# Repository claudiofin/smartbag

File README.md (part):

# SmartBag

**A removable smart insert for a handbag that recognises what is inside it —
without putting a tag on anything.**

Everything in this repo is generated by script: the PCB, the CAD, the renders,
the films. One command runs the whole chain, from KiCad to a finished MP4.

> *The GIF above is a short preview — click it for the full film.*
>
> **[▶ smartbag.mp4](media/smartbag.mp4)** (23 s) — how it is built ·
> **[▶ smartbag_sequence.mp4](media/smartbag_sequence.mp4)** (22 s) — how it works

---

## Read this first

This is a **design study**. Some of it is now checked by machine; none of it has
been built.

| | |
|---|---|
| schematic | **exists**, generated from `hardware/netlist.py`. **ERC: 0 violations.** |
| board | **113 footprints, six copper layers, routed, assembled on both sides.** DRC: **0 unconnected, 0 clearance violations, 0 shorts**; ERC clean. ⛔ It took a stackup change to get there, and the number that justified it is in [Six layers](#six-layers-and-the-number-that-decided-it). |
| part numbers | ⭐ **every IC is a real part, and its pinout comes from its own datasheet.** `tools/bom_report.py` measures each footprint against the datasheet's package on every run: **23 of 23 agree** — see [The bill of materials](#the-bill-of-materials). |
| firmware | the wake-up chain, the ledger, the taxel driver, the charge policy, the sensor bring-up, **the sensing loop that finally calls `sb_feed()`** and an Arducam Mega driver written from its own register table — **1035 assertions**, `-Werror`. ⭐ **And it builds for the nRF54L15**: [`firmware/target/`](firmware/target/) is a Zephyr app — ten HAL functions, the GATT service, the PMIC through Nordic's driver, a pin map **generated from the netlist** — at **177 KB of flash and 72 KB of RAM**, run by `tools/verify.sh`. ⚠️ Built, never run: nothing has met silicon. |
| recognition on the real part | the SoC has **no NPU**, so it was costed: 6.99 M MACs a frame on a 128 MHz M33 is **110–191 ms** against a settle window of 2000 ms — see [Recognition fits](#recognition-fits-the-processor). |
| recognition | an **enrolment pipeline that runs and is measured** — see [Recognition](#recognition). ⚠️ It now has to run on a Cortex-M33, not an NPU. |
| app | **written and running** — [`app/`](app/), tested against the firmware's own bytes. No native build; it is a web app. |
| RF | full-wave simulation rejected the antenna, closed-form analysis then rejected the whole feed — and the real part **dissolved the problem**: 60 GHz silicon has the antenna inside the package. There is now **no 60 GHz copper on this board.** See [RF](#rf). |
| thermal | **analysed** ([`thermal/budget.py`](thermal/budget.py)). It asked for charge current to be a function of cell temperature; the cell now has an NTC **in the pack**, a PMIC that reads it, and a policy under 544 assertions. |
| the taxel front end | measured wrong, then **fixed in hardware**: six transimpedance amplifiers and a 16:1 multiplexer — see [The taxel matrix](#the-taxel-matrix). |
| the 2.4 GHz antenna | ⛔ its datasheet found **three errors** in this design, one of them a terminal tied to ground that the part marks NC — see [The antenna](#the-antenna). |
| the optics flex | **exists now.** J1 was a connector to nothing for the whole project: the camera, the illuminators and the ToF live here. DRC 0 errors, 1 unconnected item. |
| the taxel sheet | **exists now.** 96 interdigitated sites, 16 columns and 6 rows, no components. **DRC 0 errors, 0 unconnected pads.** |
| fabrication | Gerbers for **all six copper layers**, drill, placement, DRC reports and a generated fab note for all three boards: `tools/fab.sh`. ⛔ The copper layer list is read out of the board file now — it was typed by hand, the stackup grew, and the next run plotted a six-layer board as four with In3 and In4 simply absent from the zip. ⚠️ **Two assembly sides now** — the processor's four decoupling capacitors are underneath it. |
| wireless power | ⛔ there was **no Qi receiver**: a coil was wired straight into a PMIC input that wants 4.0–5.5 V DC. There is now a BQ51013B, a dual resonant tank computed from the coil's own inductance, and a rectifier — see [Wireless power](#wireless-power). |

Run everything that can be checked:

```bash
./tools/verify.sh
```

```
== design constraints ==   all constraints hold
== firmware ==             28 + 324 + 53 + 264 + 21 checks, 0 failures
== protocol ==             15 tests passed
== ERC ==                  0 violations
== DRC ==                  0 errors · 4 unconnected pads · 0 footprint errors
== the other two boards == optics 0 errors, 2 pads · taxels 0 errors, 0 pads
== BOM vs footprints ==    23 of 23 named parts have a real MPN whose package fits
== recognition ==          ⭐ IT FITS, AND WITH ROOM
== physics ==              ✅ the 60 GHz feed question is settled
                           ⛔ Charging as specified puts the cell over its limit.
```

⚠️ The last two lines are printed on every run **on purpose** — and they are the
two findings that **rewrote the board**. The feed loss deleted the 60 GHz copper
and split one transceiver into two sensors; the charging analysis added a
thermistor and chose the PMIC. One is now a ✅ and one is still a ⛔, and both
keep printing: a suite that only reported its passes would be helping to forget
why the design looks the way it does.

## What it is

An **organiser that drops into any handbag** and knows what is inside it,
without tags on the objects:

| | |
|---|---|
| **IR camera** at the mouth | classifies each object as it enters or leaves |
| **60 GHz radar**, two 2×4 patch arrays | maps the volume through fabric — *where* it landed |
| **96-taxel FSR floor** | mass and footprint — *how heavy* and *what shape* |
| **ToF + Hall sensor** | the wake-up chain: closure opens → object enters → camera fires |
| **IMU** | integrates disturbance: tells the map when it has gone stale |

The bag itself is never modified, so the bag's value is never touched. The
insert slides out and moves to another one.

## The films

### smartbag_sequence.mp4 — how it works

1. **the zip opens** — the slider runs, the mouth gapes, the Hall sensor on the
   closure wakes the system
2. **an object goes in** — the ToF intercepts it crossing the mouth
3. **the IR camera fires** — three frames as it passes; the object itself lights
   up under the flash
4. **the radar maps the volume** — where it landed
5. **the FSR matrix weighs it** — the taxels under the object light up *when it
   lands*, not before
6. the zip closes again

### smartbag.mp4 — how it is built

The bag opens in section, the insert comes apart into its five layers with the
real KiCad board on top, the taxels light in a wave under the contents, then it
closes.

## Stills

| | |
|---|---|
|  |  |
| the bag closed: pinched neck, zip pulled shut | the section: contents upright, radar beam, taxels lit |

---

## The pipeline

```
hardware/generate_pcb.py  ──> smartbag_core.kicad_pcb ──> KiCad raytracer renders
                                       │
                                       └─ kicad-cli export glb ──┐
cad/bag_and_insert.py     ──> 15 STL (bag + insert) ─────────────┴─> render/scenes.py
                                                                     (Blender EEVEE)
```

```bash
python3 tools/check.py             # the constraints, in ~0.1 s
./tools/pipeline.sh 1920           # circuit -> geometry -> stills   (~45 s)
./tools/render_animation.sh 1600   # 696 animation frames            (~26 min)
python3 render/build_video.py      # captions, fades, ffmpeg encode  (~3 min)
```

⭐ **`tools/check.py` asserts what the renders discovered.** Every constraint in
it was found the expensive way — modelling something, rendering it, and seeing
it was wrong. A board 51 mm deep in a 4 mm collar wall; an FSR tail 40 mm long
against a 150 mm drop; an object landing on top of a divider. None of those
raise an error anywhere: they produce a picture that looks fine until you look
closely. Written down as assertions they cannot silently come back — and the
first time it ran it caught three more, all invisible in the renders because
something else happened to be in front.

⭐ **It is a chain, not three separate things.** The PCB does not end up in a
PDF: it is exported to GLB and becomes an object in the *same Blender scene* as
the bag. That is the only way to find out that a board does not fit where it was
supposed to — and that is exactly what happened.

## Real numbers

| | |
|---|---|
| bag | 240×95 (floor) → 276×112 at 190 mm, 3.5 mm leather; soft neck 190→245 mm |
| insert | 225 × 78 × 180 mm, removable |
| board | 196 × 20 mm strip, 0.6 mm rigid islands on 2-layer polyimide flex |
| FSR matrix | 16 columns × 6 rows = 96 taxels, 22 lines on a 24-way FFC |
| radar arrays | 2 × (2×4 patches), 2.5 mm pitch = λ₀/2 at 60 GHz |
| battery | **Jauch LP523450JU**, 950 mAh, 53 × 34.5 × 5.8 mm, with PCM and a 10 k NTC on its harness — beside the Qi coil, not on top of it |

## What the renders actually rejected

This is the part worth reading. Putting the PCB and the CAD in the *same scene*
killed several things that looked fine on paper:

- **The first board layout was impossible.** A 126×51 mm cross with the FSR tail
  dropping out of the middle. Dropped into the insert, a board 51 mm deep either
  spans the mouth floating in mid-air or pokes out of the bag: the collar wall is
  4 mm. Redrawn as a **196 × 20 strip** sitting in a 24 mm front band.
- **The FSR tail on the board did not reach the floor.** 40 mm of flex against a
  150 mm drop. It became a **separate FFC** on J4 — which is also how it would
  really be assembled, because the cable has to pull out.
- **The insert has to pass through the smallest cross-section**, the floor, not
  the mouth. Hence 225×78 and not 240×82.
- **The bag never actually closed.** It was an open-mouthed tote, so the only
  thing "opening" was the section. Without a real closure there is no Hall
  sensor either — and that is the first link in the whole chain.
- **A zip is not a hinge; it is a mouth that pinches shut.** Four attempts
  rotated two rigid flaps hinged on the rim (up, down, inwards, outwards). All
  four read as a *hatch*, because two rigid plates rotating about a hinge **are**
  a hatch. The problem was upstream: a bag modelled as a rigid box cannot have a
  credible closure. The rigid body now ends at 190 mm and the last 55 are a
  **soft neck** — a surface with two states (oval mouth / mouth pinched to
  11 mm) interpolated by a shape key. The two rows of teeth do not rotate, they
  **separate**.
- **A zip has to be able to end somewhere.** With a rounded-rectangle mouth the
  teeth stayed 100 mm apart even at the tips and the slider finished its travel
  floating in mid-air. The mouth is now a **pointed oval**: the depth is squeezed
  to 4.5% over the last 40 mm, and only in the upper part of the neck (t³ —
  applied in proportion to height, the ends became wedges and from the side the
  bag looked like it had a pitched roof).
- **The object landed inside another object.** It fell at x = 44, straddling the
  divider at x = 37.5. Moved to x = 60, checked against divider, pouch and keys.
  The number lives in one place, `CONTENTS`, and both the render and the taxel
  logic read it from there.
- **The camera did not exist.** There was a pink cone flashing, but no module
  emitting it: light came out of a hole in the microfibre. A sensor you cannot
  see is a sensor nobody understands. There is now a module with its lens and
  four illuminators — and the **object lights up too**, which is the only thing
  that makes clear the flash is hitting it.
- **The hand was deleted.** Four attempts (from above, tilted, in section, with
  tapered and curled phalanges) and it stayed the worst thing in the frame while
  stealing attention from the sensors. An object descending on its own is
  understood in the first frame and has nothing to get wrong.

## The circuit

The connectivity is declared once, in [`hardware/netlist.py`](hardware/netlist.py):
pins, electrical types and nets for 26 parts. Three things consume it — the
schematic generator, the board generator, and the checks — so the board and the
schematic cannot drift apart. `kicad-cli pcb drc --schematic-parity` reports
**0 footprint errors**, which is that claim, verified.

**ERC found two things that were genuinely missing**, and the fix was to add
them rather than to silence the check:

- **no way to program the board.** SWDIO and SWCLK went nowhere. There is now a
  4-way SWD connector (J5), with its pins declared *bidirectional*, which is
  both electrically accurate and what makes ERC see the SoC's SWCLK input as
  driven.
- **a BLE radio with no antenna.** The SoC's ANT pin connected to nothing. There
  is now a 2.4 GHz chip antenna (AE1).

**DRC went from 439 violations to 0**, and almost all of the reduction was
deleting something rather than adding it:

| | |
|---|---|
| 439 → 215 | the board never declared its process. It is 0.1 mm lines on 2-layer polyimide flex with 0.3/0.15 vias; judged against KiCad's generic 0.2 mm defaults it collected 108 track-width and 112 via/drill violations that said nothing about the layout. |
| 215 → 1 | **the decorative routing.** Before there was a netlist, the generator drew bundles of tracks on net 0 to make the renders look like a circuit. Once the pads carried real nets, DRC read those tracks for what they were: 40 shorts, 6 clearance violations, 168 solder-mask bridges — one object producing more than half the errors on the board. |
| 1 → 0 | a courtyard overlap, and silkscreen. |

⛔ **The board is not routed.** Fanning out a 0.4 mm-pitch QFN-48, laying a
22-line bus and two 60 GHz microstrip feeds is a real job, and faking it with
decorative polylines is exactly the mistake that was just removed.

## RF

[`rf/patch_sim.py`](rf/patch_sim.py) solves Maxwell's equations on the patch
element with openEMS — ground plane, dielectric, patch, probe feed — and it
**falsified the antenna as first drawn**.

The setup is validated first, because a negative result is only worth stating if
the same solver reproduces a case theory says should work: a patch sized by the
transmission-line model (1.31 mm on 0.127 mm) comes back at **59.0 GHz, −9.3 dB**
— within 1.7% of target.

| substrate | patch | f_res | S11 | −10 dB BW | |
|---|---|---|---|---|---|
| 0.600 mm | 1.20 mm | 50.8 GHz | **−2.5 dB** | 0 | the rigid stack, as first drawn |
| 0.250 mm | 1.20 mm | **59.9 GHz** | **−27.2 dB** | **3.5 GHz** | the antenna islands, as now specified |

⛔ **On the 0.6 mm rigid stack the element does not work.** It sits 9 GHz low and
reflects almost everything. `h/λ₀` was 0.12, which is enormous at 60 GHz — the
board is 0.6 mm because that is what the rigid islands are, and nobody had
chosen that number for the antenna.

⭐ **The fix is the stackup, not the artwork.** At 0.25 mm the *same* 1.2 mm patch
matches at −27.2 dB with 3.5 GHz of bandwidth. On a rigid-flex board that costs
nothing: the antenna areas keep the flex core and a thin stiffener instead of the
full rigid buildup. A `.kicad_pcb` carries one board thickness, so it is a
fabrication note, on the Cmts.User layer and in `dimensions.py`.

⚠️ One element in isolation. No array coupling, no flex bend, no connector
parasitics, and εr is assumed — the numbers move with it.

**Getting the simulation to run at all took four wrong hypotheses.** It kept
returning `Energy: ~ nan` from the first timestep, and PML-over-a-conductor, the
lossy dielectric and the port were all blamed before a uniform-mesh control case
came back clean and pinned it on **mesh grading**: a 16:1 jump from the cells
over the patch to the far field. FDTD does not error on that, it silently
returns NaN. `rf/patch_sim.py` now refuses to run a mesh that will diverge, which
turns ninety wasted seconds into one line of output.

```bash
python3 rf/patch_sim.py --sweep
```

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
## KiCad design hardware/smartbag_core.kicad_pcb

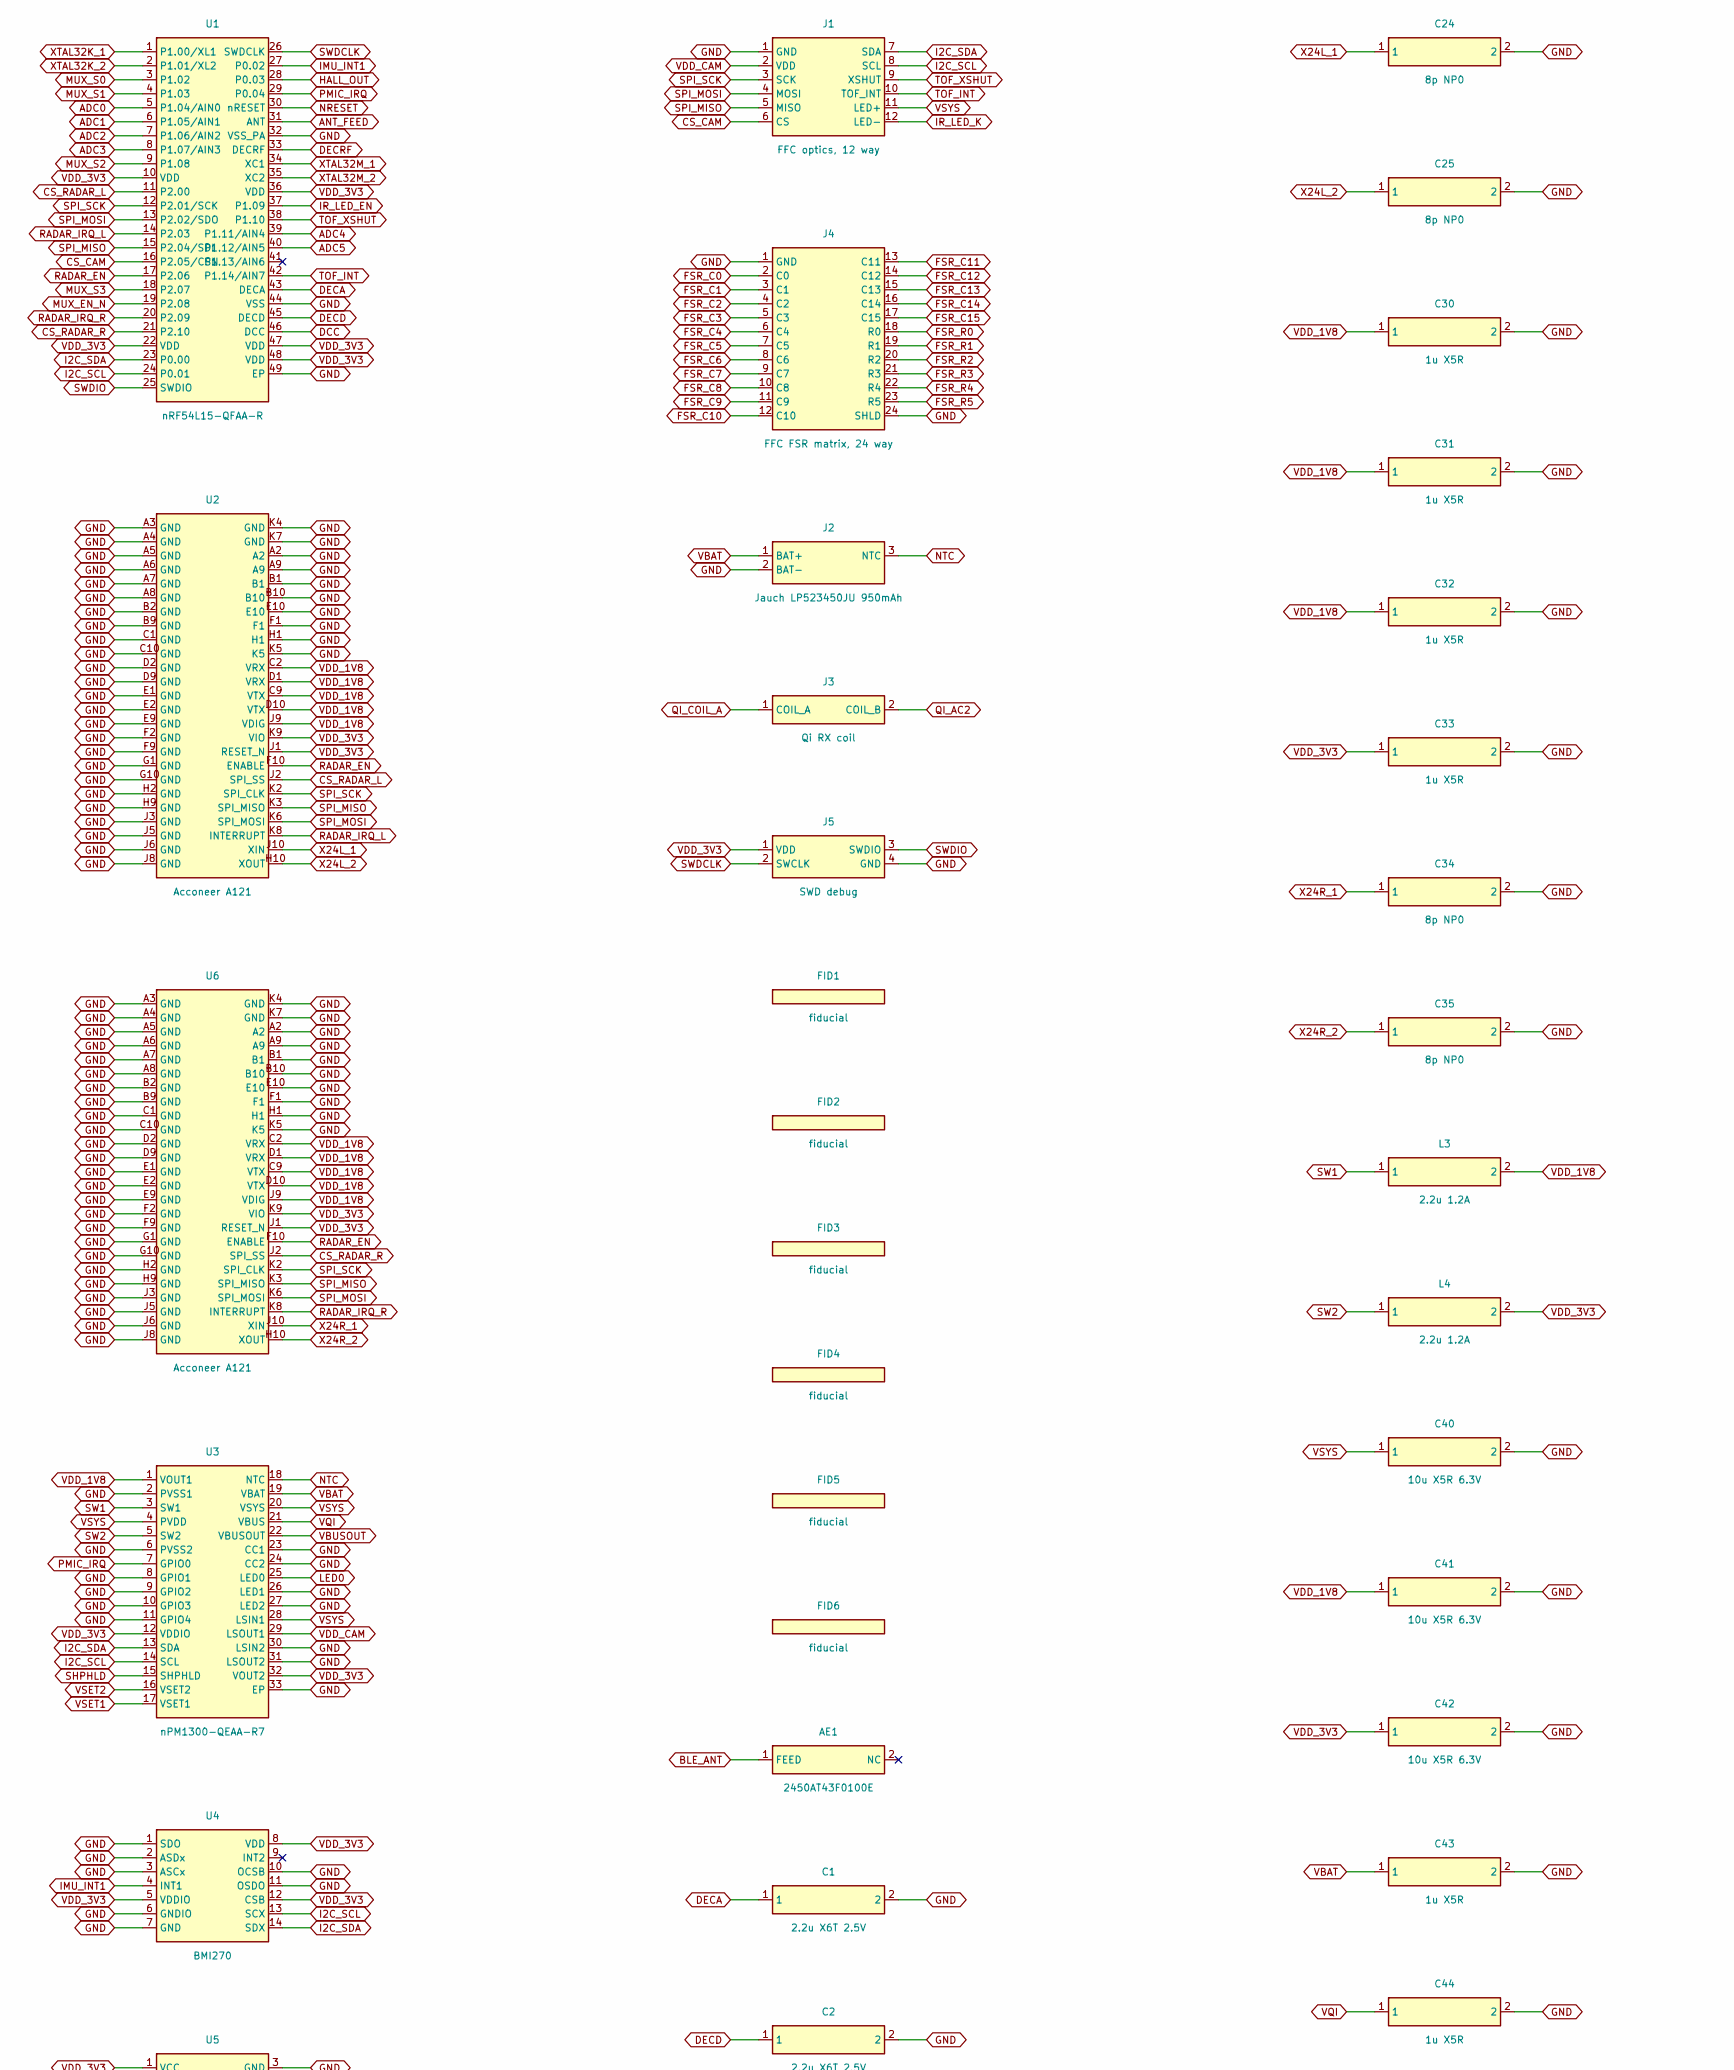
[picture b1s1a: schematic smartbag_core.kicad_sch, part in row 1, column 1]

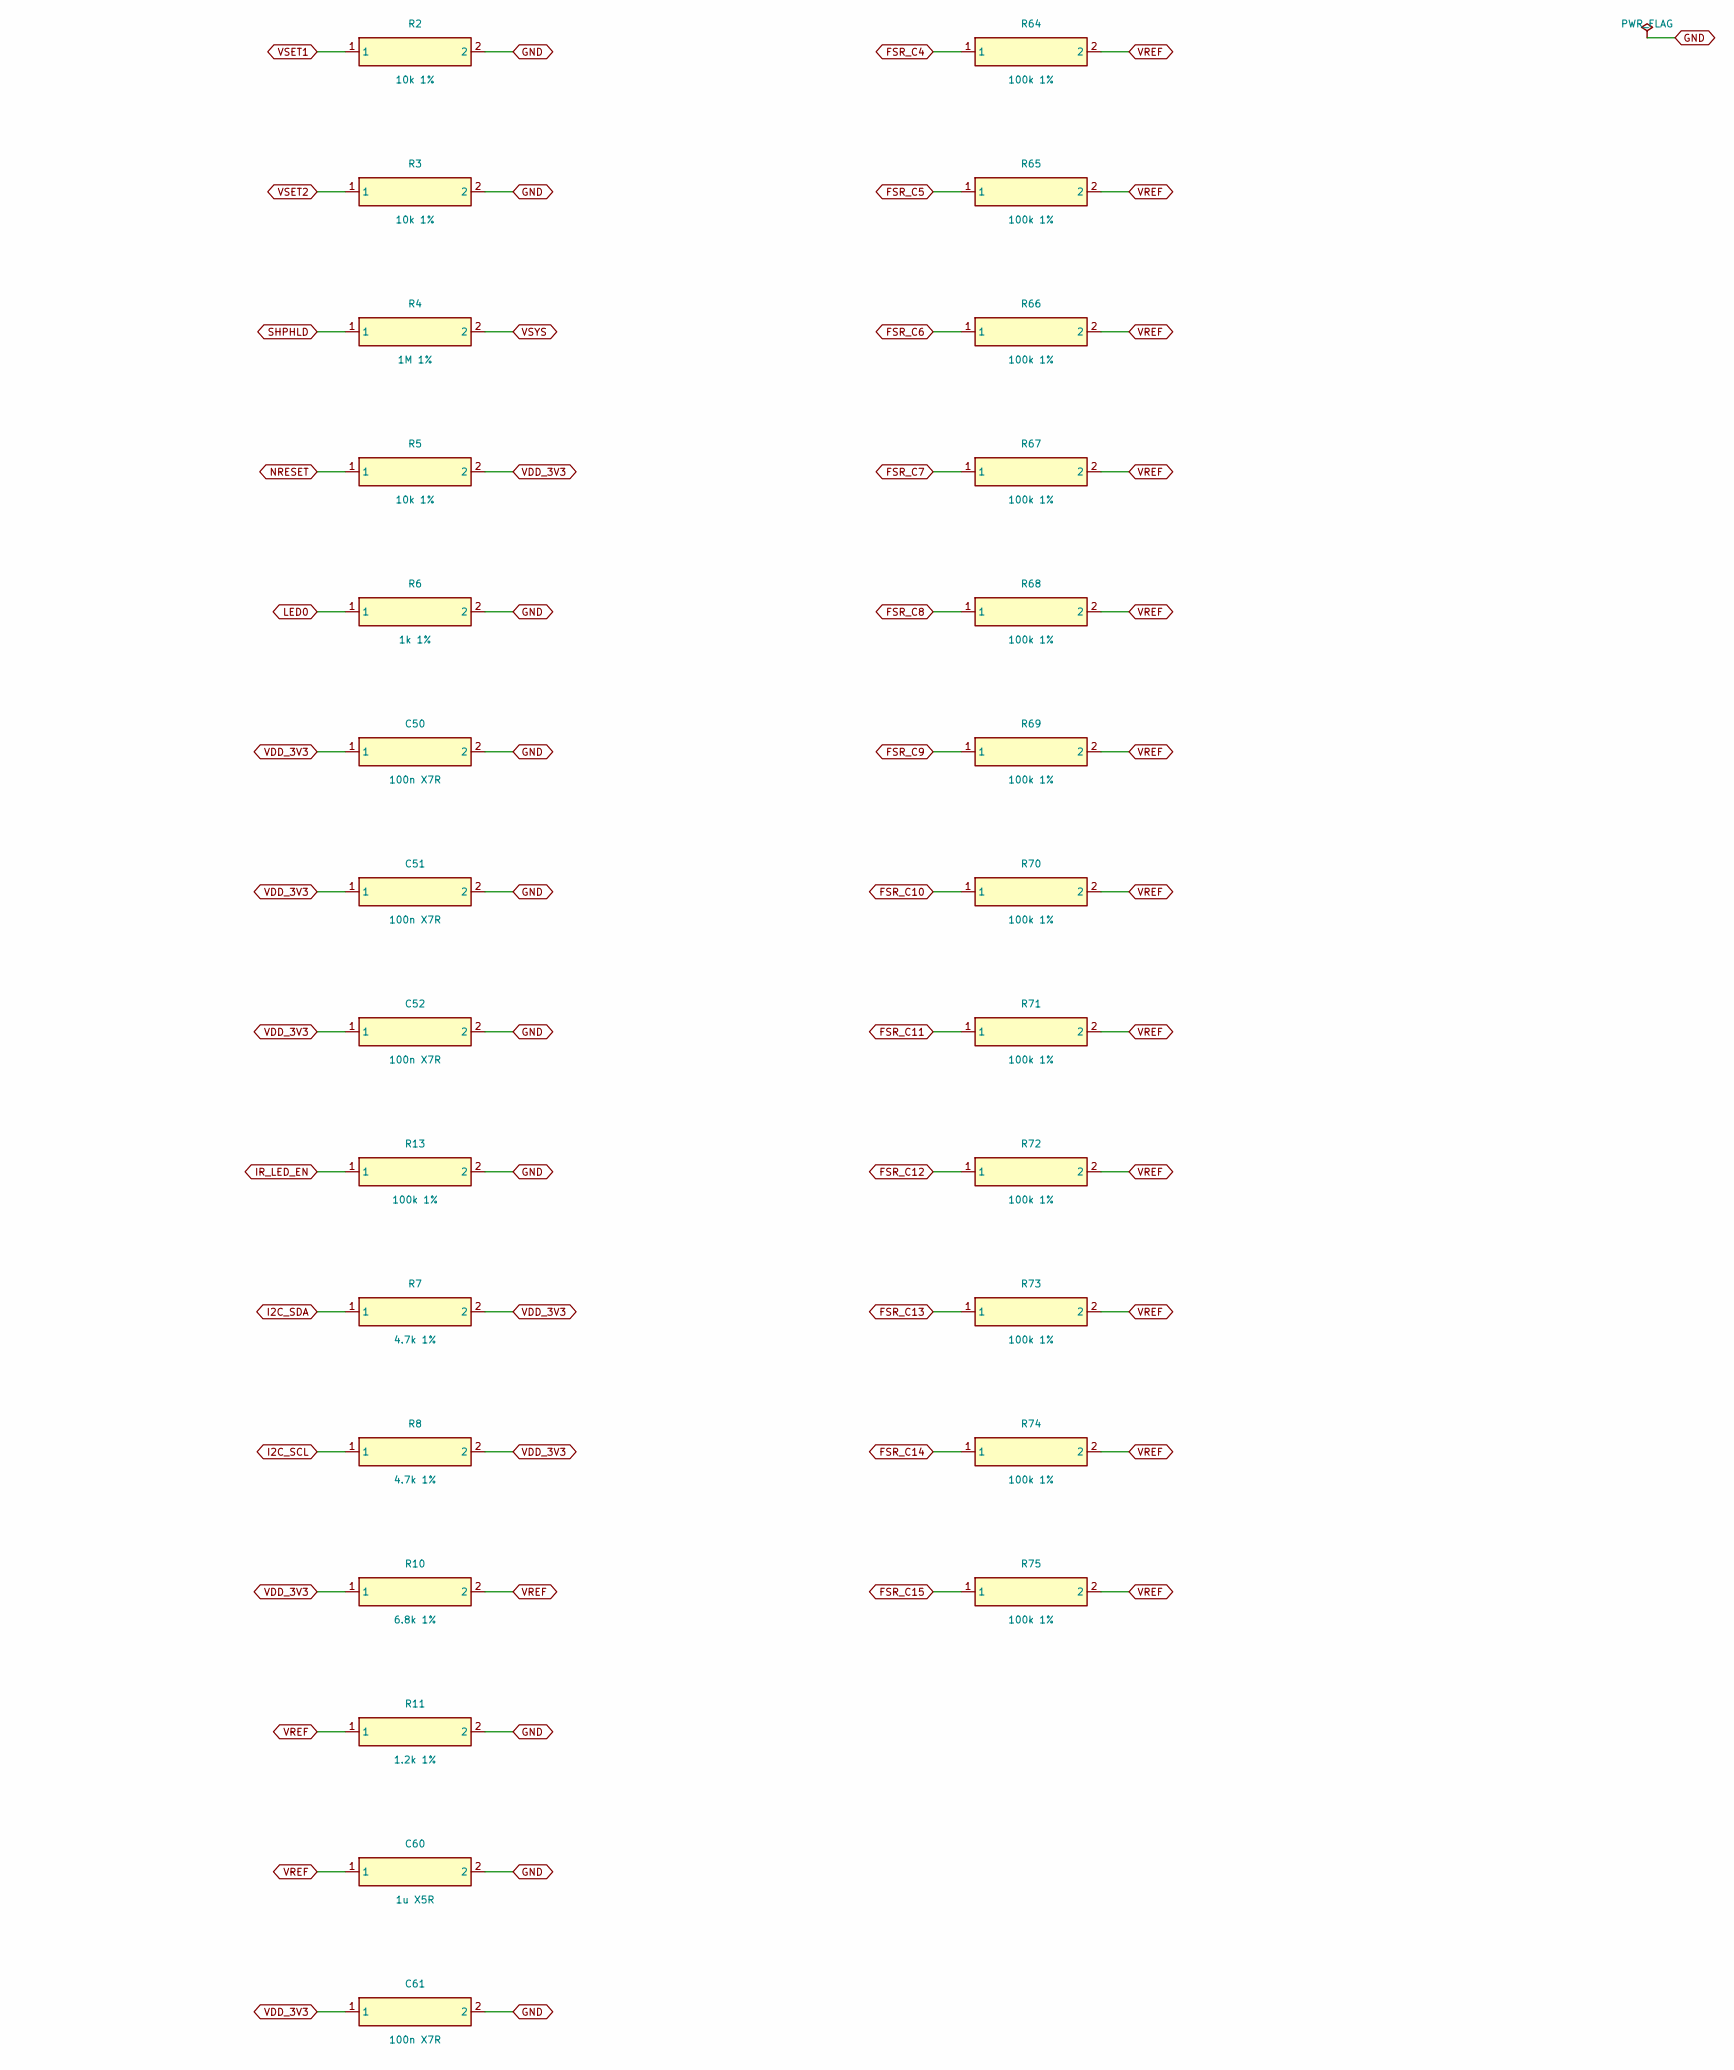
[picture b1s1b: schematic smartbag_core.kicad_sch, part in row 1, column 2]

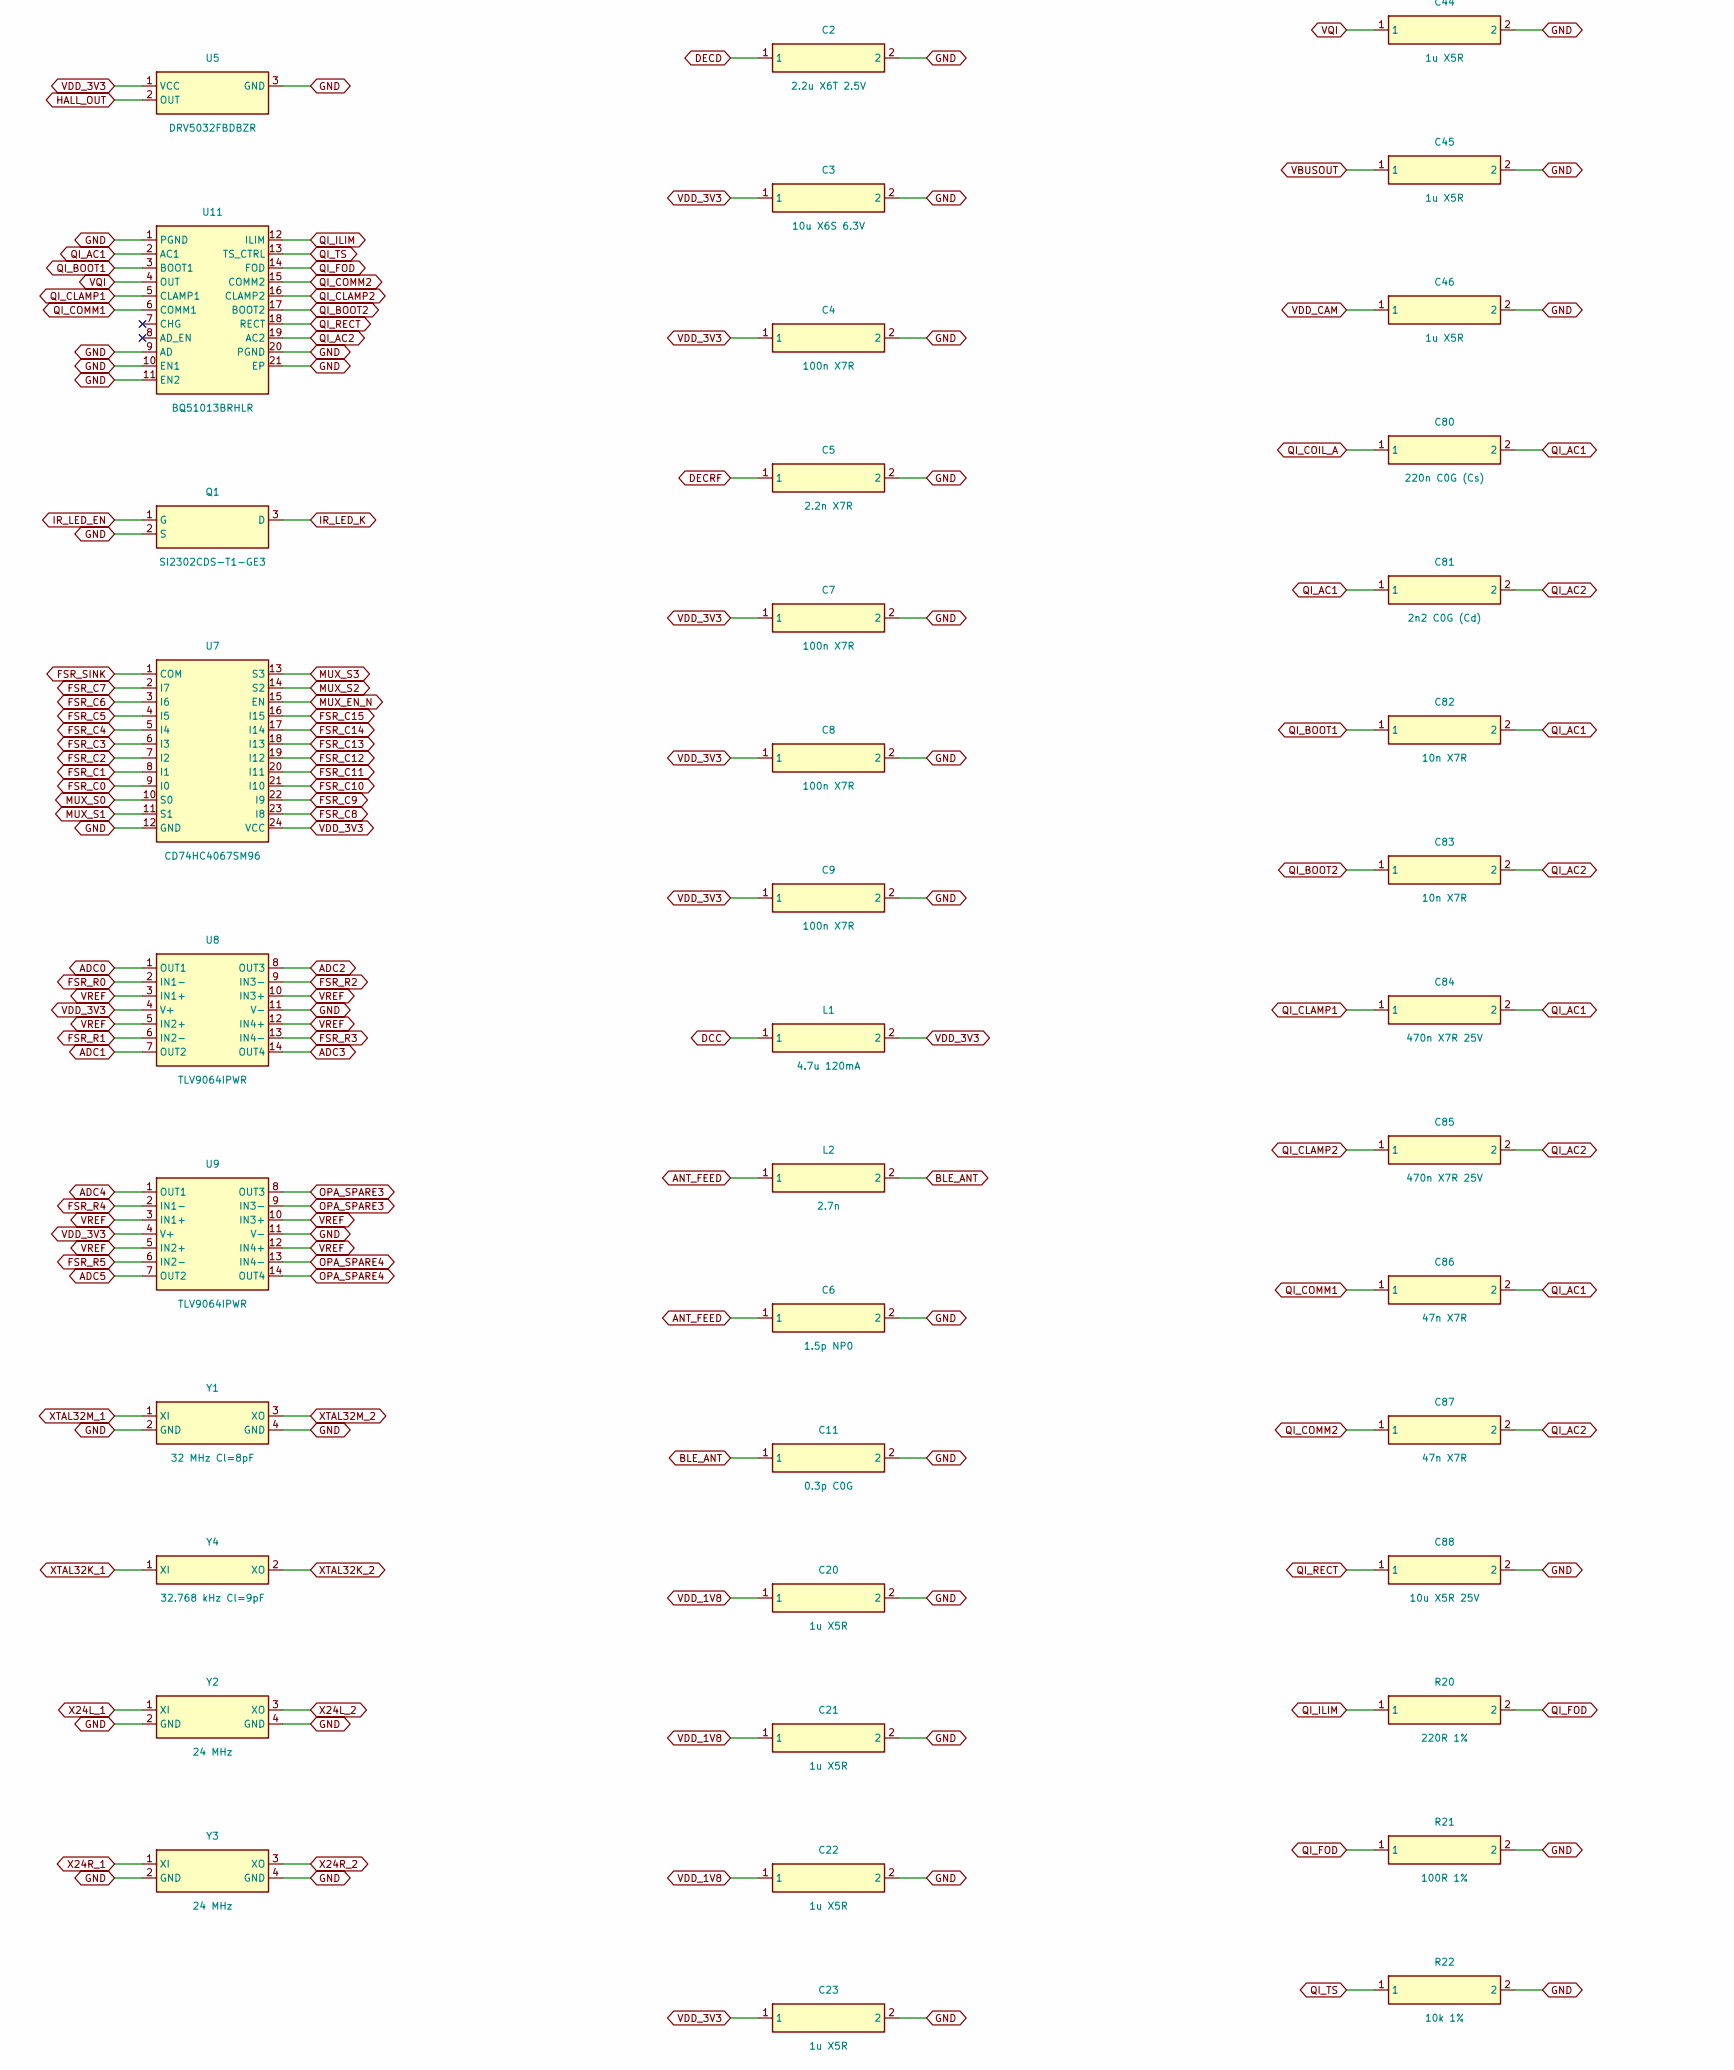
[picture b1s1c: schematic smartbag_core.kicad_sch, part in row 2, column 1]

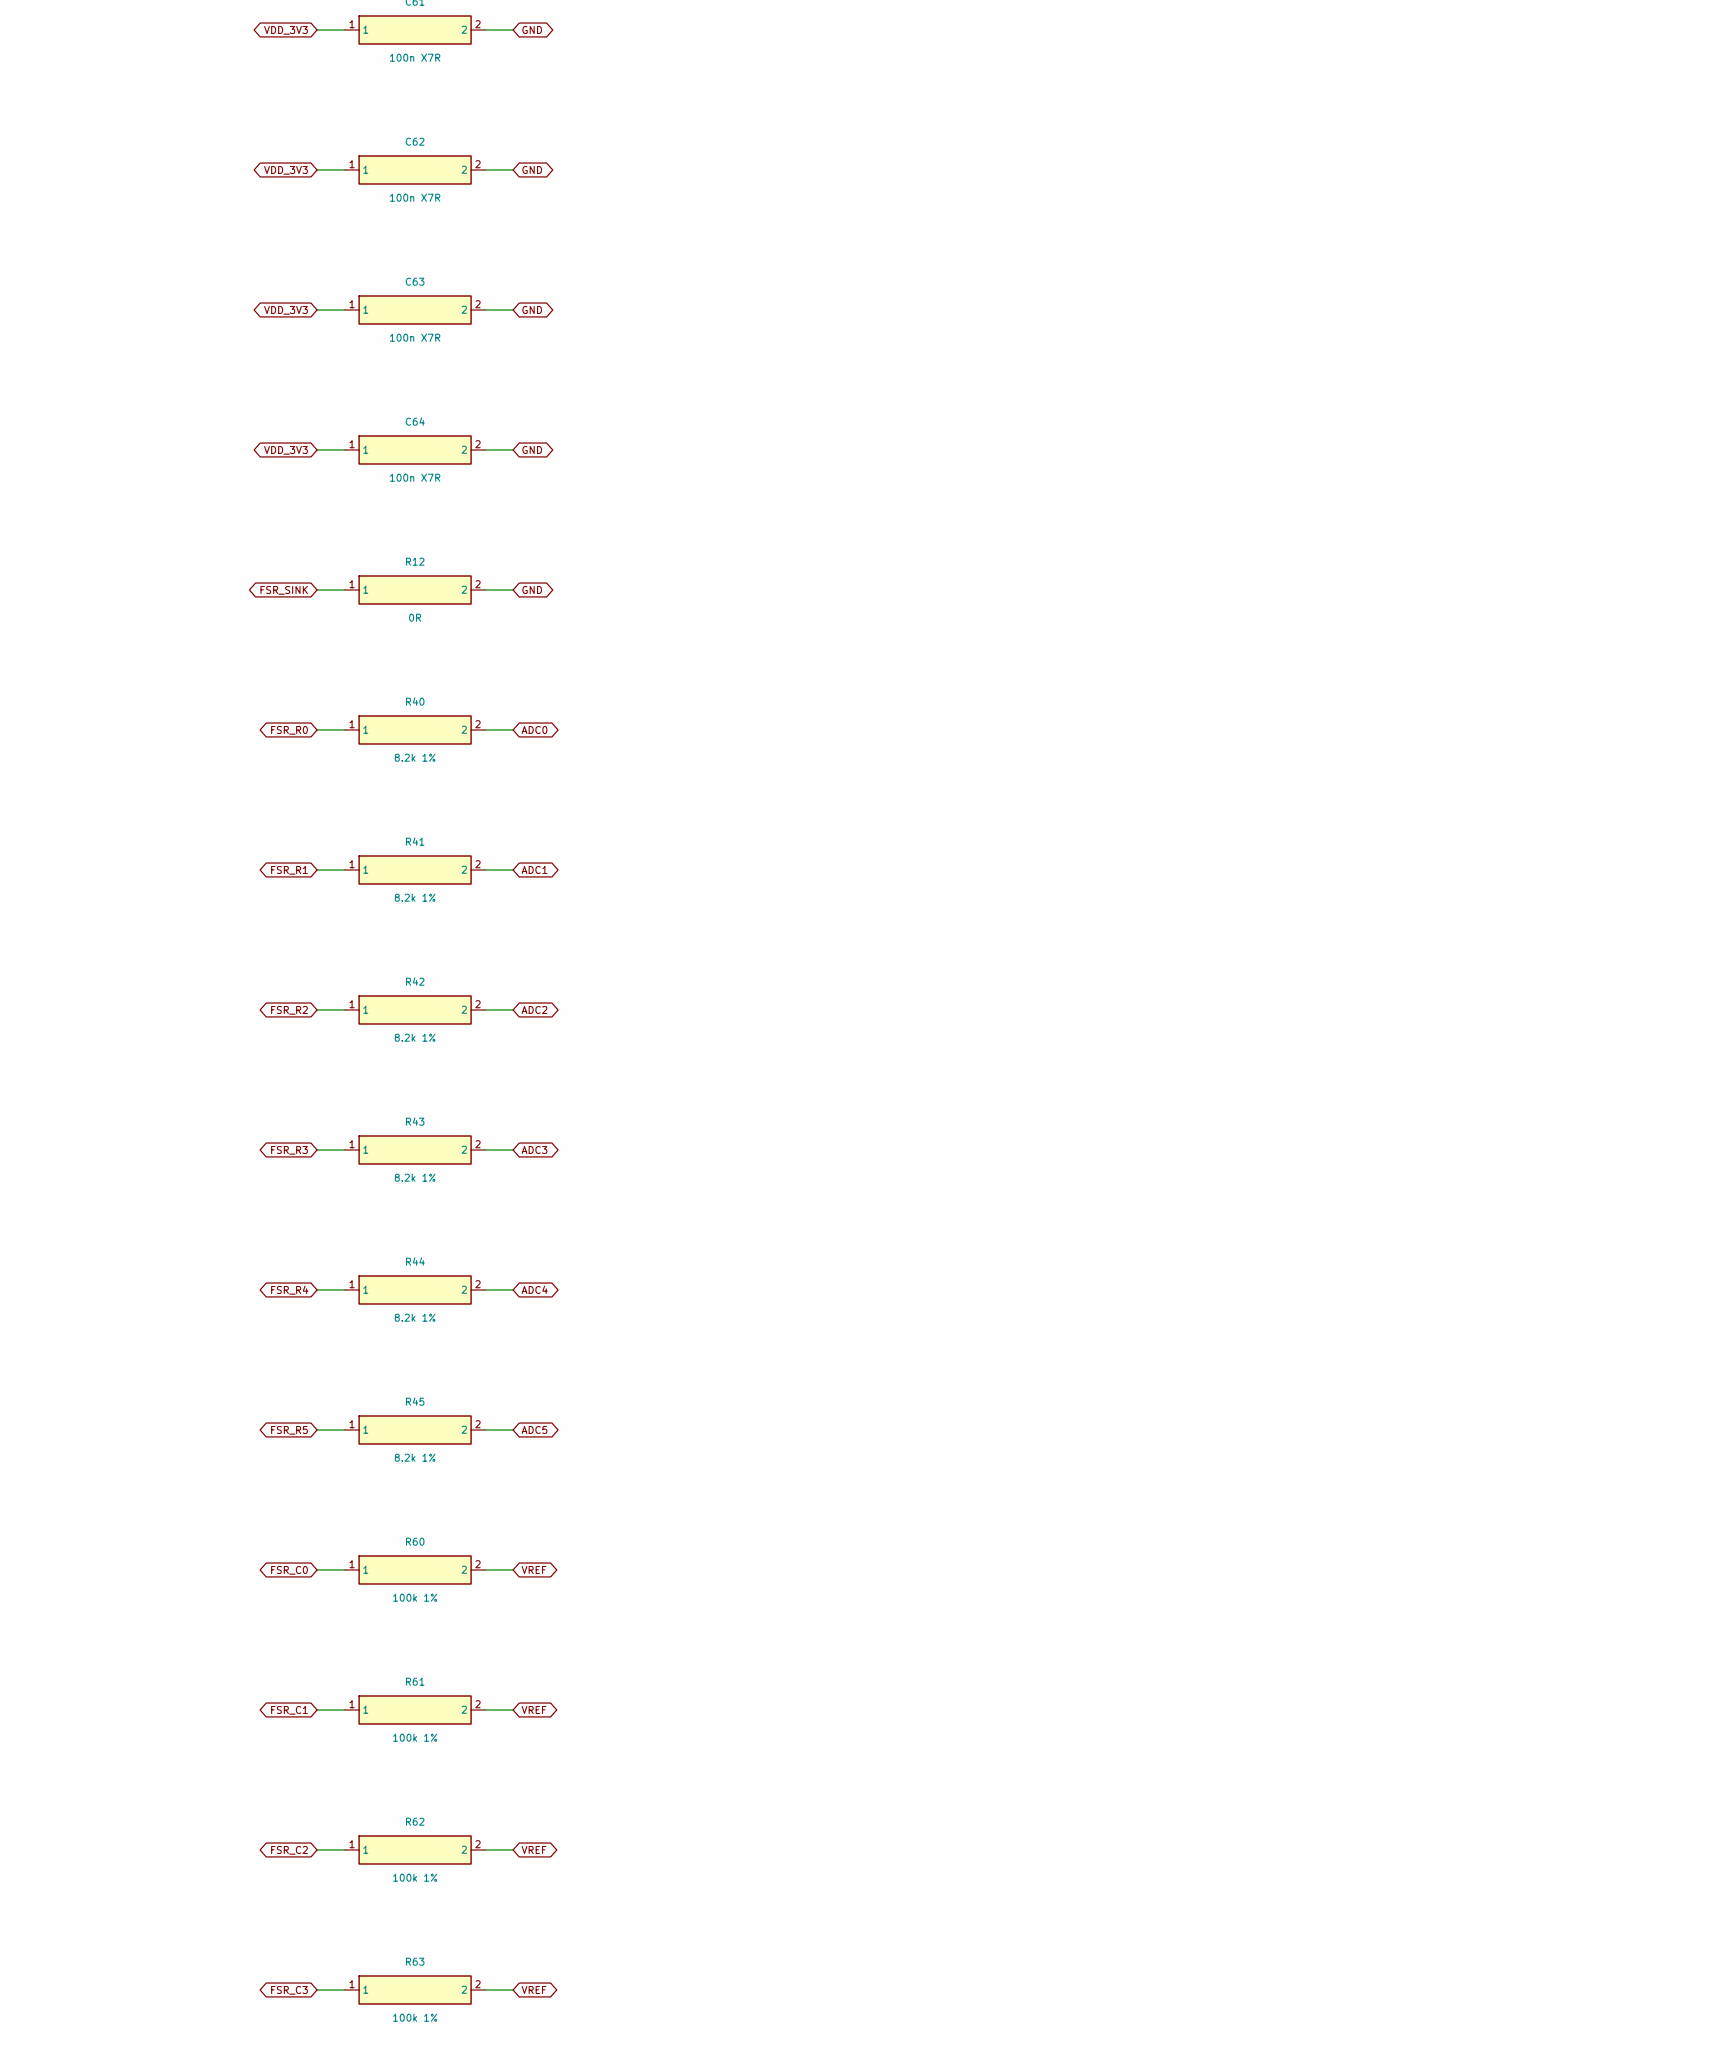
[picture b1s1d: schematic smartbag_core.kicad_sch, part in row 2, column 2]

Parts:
AE1: 2450AT43F0100E; Johanson_2450AT43F0100_2400-2500Mhz
C1, C2: 2.2u X6T 2.5V; C_0402_1005Metric
C3: 10u X6S 6.3V; C_0402_1005Metric
C4, C7, C8, C9, C50, C51, C52, C61, C62, C63, C64: 100n X7R; C_0402_1005Metric
C5: 2.2n X7R; C_0402_1005Metric
C6: 1.5p NP0; C_0402_1005Metric
C11: 0.3p C0G; C_0402_1005Metric
C20, C21, C22, C23, C30, C31, C32, C33, C43, C44, C45, C46, C60: 1u X5R; C_0402_1005Metric
C24, C25, C34, C35: 8p NP0; C_0402_1005Metric
C40, C41, C42: 10u X5R 6.3V; C_0402_1005Metric
C80: 220n C0G (Cs); C_0603_1608Metric
C81: 2n2 C0G (Cd); C_0402_1005Metric
C82, C83: 10n X7R; C_0402_1005Metric
C84, C85: 470n X7R 25V; C_0603_1608Metric
C86, C87: 47n X7R; C_0402_1005Metric
C88: 10u X5R 25V; C_0603_1608Metric
FID1, FID2, FID3, FID4, FID5, FID6: fiducial; Fiducial_1mm_Mask2mm
J1: FFC optics, 12 way; Hirose_FH12-12S-0.5SH_1x12-1MP_P0.50mm_Horizontal
J2: Jauch LP523450JU 950mAh; JST_PH_S3B-PH-K_1x03_P2.00mm_Horizontal
J3: Qi RX coil; JST_SH_SM02B-SRSS-TB_1x02-1MP_P1.00mm_Horizontal
J4: FFC FSR matrix, 24 way; Hirose_FH12-24S-0.5SH_1x24-1MP_P0.50mm_Horizontal
J5: SWD debug; JST_SH_SM04B-SRSS-TB_1x04-1MP_P1.00mm_Horizontal
L1: 4.7u 120mA; L_0603_1608Metric
L2: 2.7n; L_0402_1005Metric
L3, L4: 2.2u 1.2A; L_0603_1608Metric
Q1: SI2302CDS-T1-GE3; SOT-23
R2, R3, R5, R22: 10k 1%; R_0402_1005Metric
R4: 1M 1%; R_0402_1005Metric
R6: 1k 1%; R_0402_1005Metric
R7, R8: 4.7k 1%; R_0402_1005Metric
R10: 6.8k 1%; R_0402_1005Metric
R11: 1.2k 1%; R_0402_1005Metric
R12: 0R; R_0402_1005Metric
R13, R60, R61, R62, R63, R64, R65, R66, R67, R68, R69, R70, R71, R72, R73, R74, R75: 100k 1%; R_0402_1005Metric
R20: 220R 1%; R_0402_1005Metric
R21: 100R 1%; R_0402_1005Metric
R40, R41, R42, R43, R44, R45: 8.2k 1%; R_0402_1005Metric
U1: nRF54L15-QFAA-R; QFN-48-1EP_6x6mm_P0.4mm_EP4.6x4.6mm
U2, U6: Acconeer A121; Acconeer_A121_fcCSP50
U3: nPM1300-QEAA-R7; QFN-32-1EP_5x5mm_P0.5mm_EP3.45x3.45mm
U4: BMI270; Bosch_LGA-14_3x2.5mm_P0.5mm
U5: DRV5032FBDBZR; SOT-23
U7: CD74HC4067SM96; SSOP-24_5.3x8.2mm_P0.65mm
U8, U9: TLV9064IPWR; TSSOP-14_4.4x5mm_P0.65mm
U11: BQ51013BRHLR; Texas_VQFN-RHL-20
Y1: 32 MHz Cl=8pF; Crystal_SMD_2016-4Pin_2.0x1.6mm
Y2, Y3: 24 MHz; Crystal_SMD_2016-4Pin_2.0x1.6mm
Y4: 32.768 kHz Cl=9pF; Crystal_SMD_2012-2Pin_2.0x1.2mm

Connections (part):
ADC0: R40.2, U1.5 (P1.04/AIN0), U8.1 (OUT1)
ADC1: R41.2, U1.6 (P1.05/AIN1), U8.7 (OUT2)
ADC2: R42.2, U1.7 (P1.06/AIN2), U8.8 (OUT3)
ADC3: R43.2, U1.8 (P1.07/AIN3), U8.14 (OUT4)
ADC4: R44.2, U1.39 (P1.11/AIN4), U9.1 (OUT1)
ADC5: R45.2, U1.40 (P1.12/AIN5), U9.7 (OUT2)
ANT_FEED: C6.1, L2.1, U1.31 (ANT)
BLE_ANT: AE1.1 (FEED), C11.1, L2.2
CS_CAM: J1.6 (CS), U1.16 (P2.05/CSN)
CS_RADAR_L: U1.11 (P2.00), U2.J2 (SPI_SS)
CS_RADAR_R: U1.21 (P2.10), U6.J2 (SPI_SS)
DCC: L1.1, U1.46 (DCC)
DECA: C1.1, U1.43 (DECA)
DECD: C2.1, U1.45 (DECD)
DECRF: C5.1, U1.33 (DECRF)
FSR_C0: J4.2 (C0), R60.1, U7.9 (I0)
FSR_C1: J4.3 (C1), R61.1, U7.8 (I1)
FSR_C2: J4.4 (C2), R62.1, U7.7 (I2)
FSR_C3: J4.5 (C3), R63.1, U7.6 (I3)
FSR_C4: J4.6 (C4), R64.1, U7.5 (I4)
FSR_C5: J4.7 (C5), R65.1, U7.4 (I5)
FSR_C6: J4.8 (C6), R66.1, U7.3 (I6)
FSR_C7: J4.9 (C7), R67.1, U7.2 (I7)
FSR_C8: J4.10 (C8), R68.1, U7.23 (I8)
FSR_C9: J4.11 (C9), R69.1, U7.22 (I9)
FSR_C10: J4.12 (C10), R70.1, U7.21 (I10)
FSR_C11: J4.13 (C11), R71.1, U7.20 (I11)
FSR_C12: J4.14 (C12), R72.1, U7.19 (I12)
FSR_C13: J4.15 (C13), R73.1, U7.18 (I13)
FSR_C14: J4.16 (C14), R74.1, U7.17 (I14)
FSR_C15: J4.17 (C15), R75.1, U7.16 (I15)
FSR_R0: J4.18 (R0), R40.1, U8.2 (IN1-)
FSR_R1: J4.19 (R1), R41.1, U8.6 (IN2-)
FSR_R2: J4.20 (R2), R42.1, U8.9 (IN3-)
FSR_R3: J4.21 (R3), R43.1, U8.13 (IN4-)
FSR_R4: J4.22 (R4), R44.1, U9.2 (IN1-)
FSR_R5: J4.23 (R5), R45.1, U9.6 (IN2-)
FSR_SINK: R12.1, U7.1 (COM)
GND: C1.2, C2.2, C3.2, C4.2, C5.2, C6.2, C7.2, C8.2, C9.2, C11.2, C20.2, C21.2, C22.2, C23.2, C24.2, C25.2, C30.2, C31.2, C32.2, C33.2, C34.2, C35.2, C40.2, C41.2, C42.2, C43.2, C44.2, C45.2, C46.2, C50.2, C51.2, C52.2, C60.2, C61.2, C62.2, C63.2, C64.2, C88.2, J1.1 (GND), J2.2 (BAT-), J4.1 (GND), J4.24 (SHLD), J5.4 (GND), Q1.2 (S), R2.2, R3.2, R6.2, R11.2, R12.2, R13.2, R21.2, R22.2, U1.32 (VSS_PA), U1.44 (VSS), U1.49 (EP), U2.A2, U2.A3 (GND), U2.A4 (GND), U2.A5 (GND), U2.A6 (GND), U2.A7 (GND), U2.A8 (GND), U2.A9, U2.B1, U2.B2 (GND), U2.B9 (GND), U2.B10, U2.C1 (GND), U2.C10 (GND), U2.D2 (GND), U2.D9 (GND), U2.E1 (GND), U2.E2 (GND), U2.E9 (GND), U2.E10, U2.F1, U2.F2 (GND), U2.F9 (GND), U2.G1 (GND), U2.G10 (GND)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
HALL_OUT: U1.28 (P0.03), U5.2 (OUT)
I2C_SCL: J1.8 (SCL), R8.1, U1.24 (P0.01), U3.14 (SCL), U4.13 (SCX)
I2C_SDA: J1.7 (SDA), R7.1, U1.23 (P0.00), U3.13 (SDA), U4.14 (SDX)
IMU_INT1: U1.27 (P0.02), U4.4 (INT1)
IR_LED_EN: Q1.1 (G), R13.1, U1.37 (P1.09)
IR_LED_K: J1.12 (LED-), Q1.3 (D)
LED0: R6.1, U3.25 (LED0)
MUX_EN_N: U1.19 (P2.08), U7.15 (EN)
MUX_S0: U1.3 (P1.02), U7.10 (S0)
MUX_S1: U1.4 (P1.03), U7.11 (S1)
MUX_S2: U1.9 (P1.08), U7.14 (S2)
MUX_S3: U1.18 (P2.07), U7.13 (S3)
NRESET: R5.1, U1.30 (nRESET)
NTC: J2.3 (NTC), U3.18 (NTC)
OPA_SPARE3: U9.8 (OUT3), U9.9 (IN3-)
OPA_SPARE4: U9.13 (IN4-), U9.14 (OUT4)
PMIC_IRQ: U1.29 (P0.04), U3.7 (GPIO0)
QI_AC1: C80.2, C81.1, C82.2, C84.2, C86.2, U11.2 (AC1)
QI_AC2: C81.2, C83.2, C85.2, C87.2, J3.2 (COIL_B), U11.19 (AC2)
QI_BOOT1: C82.1, U11.3 (BOOT1)
QI_BOOT2: C83.1, U11.17 (BOOT2)
QI_CLAMP1: C84.1, U11.5 (CLAMP1)
QI_CLAMP2: C85.1, U11.16 (CLAMP2)
QI_COIL_A: C80.1, J3.1 (COIL_A)
QI_COMM1: C86.1, U11.6 (COMM1)
QI_COMM2: C87.1, U11.15 (COMM2)
QI_FOD: R20.2, R21.1, U11.14 (FOD)
QI_ILIM: R20.1, U11.12 (ILIM)
QI_RECT: C88.1, U11.18 (RECT)
QI_TS: R22.1, U11.13 (TS_CTRL)
RADAR_EN: U1.17 (P2.06), U2.F10 (ENABLE), U6.F10 (ENABLE)
RADAR_IRQ_L: U1.14 (P2.03), U2.K8 (INTERRUPT)
RADAR_IRQ_R: U1.20 (P2.09), U6.K8 (INTERRUPT)
SHPHLD: R4.1, U3.15 (SHPHLD)
SPI_MISO: J1.5 (MISO), U1.15 (P2.04/SDI), U2.K3 (SPI_MISO), U6.K3 (SPI_MISO)
SPI_MOSI: J1.4 (MOSI), U1.13 (P2.02/SDO), U2.K6 (SPI_MOSI), U6.K6 (SPI_MOSI)
SPI_SCK: J1.3 (SCK), U1.12 (P2.01/SCK), U2.K2 (SPI_CLK), U6.K2 (SPI_CLK)
SW1: L3.1, U3.3 (SW1)
SW2: L4.1, U3.5 (SW2)
SWDCLK: J5.2 (SWCLK), U1.26 (SWDCLK)
SWDIO: J5.3 (SWDIO), U1.25 (SWDIO)
TOF_INT: J1.10 (TOF_INT), U1.42 (P1.14/AIN7)
TOF_XSHUT: J1.9 (XSHUT), U1.38 (P1.10)
VBAT: C43.1, J2.1 (BAT+), U3.19 (VBAT)
VBUSOUT: C45.1, U3.22 (VBUSOUT)
VDD_1V8: C20.1, C21.1, C22.1, C30.1, C31.1, C32.1, C41.1, L3.2, U2.C2 (VRX), U2.C9 (VTX), U2.D1 (VRX), U2.D10 (VTX), U2.J9 (VDIG), U3.1 (VOUT1), U6.C2 (VRX), U6.C9 (VTX), U6.D1 (VRX), U6.D10 (VTX), U6.J9 (VDIG)
VDD_3V3: C3.1, C4.1, C7.1, C8.1, C9.1, C23.1, C33.1, C42.1, C50.1, C51.1, C52.1, C61.1, C62.1, C63.1, C64.1, J5.1 (VDD), L1.2, L4.2, R5.2, R7.2, R8.2, R10.1, U1.10 (VDD), U1.22 (VDD), U1.36 (VDD), U1.47 (VDD), U1.48 (VDD), U2.J1 (RESET_N), U2.K9 (VIO), U3.12 (VDDIO), U3.32 (VOUT2), U4.5 (VDDIO), U4.8 (VDD), U4.12 (CSB), U5.1 (VCC), U6.J1 (RESET_N), U6.K9 (VIO), U7.24 (VCC), U8.4 (V+), U9.4 (V+)
VDD_CAM: C46.1, J1.2 (VDD), U3.29 (LSOUT1)
VQI: C44.1, U3.21 (VBUS), U11.4 (OUT)
VREF: C60.1, R10.2, R11.1, R60.2, R61.2, R62.2, R63.2, R64.2, R65.2, R66.2, R67.2, R68.2, R69.2, R70.2, R71.2, R72.2, R73.2, R74.2, R75.2, U8.3 (IN1+), U8.5 (IN2+), U8.10 (IN3+), U8.12 (IN4+), U9.3 (IN1+), U9.5 (IN2+), U9.10 (IN3+), U9.12 (IN4+)
VSET1: R2.1, U3.17 (VSET1)
VSET2: R3.1, U3.16 (VSET2)
VSYS: C40.1, J1.11 (LED+), R4.2, U3.4 (PVDD), U3.20 (VSYS), U3.28 (LSIN1)
X24L_1: C24.1, U2.J10 (XIN), Y2.1 (XI)
X24L_2: C25.1, U2.H10 (XOUT), Y2.3 (XO)
X24R_1: C34.1, U6.J10 (XIN), Y3.1 (XI)
X24R_2: C35.1, U6.H10 (XOUT), Y3.3 (XO)
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

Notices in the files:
README.md:
Licence:
MIT — see [LICENSE](LICENSE).
